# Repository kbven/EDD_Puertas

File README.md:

# Disseny de les portes

> **Autors:** Brandon Ventura, Pablo Peñalba.

> **Grup Mati**                             

--------

## Objectivo

Diseño de una una PCB para controlar las puertas.

## Especificaciones

* Mecanismo de motor para el alza cristales con un final de carrera.

* Implementación de mecanismo de seguridad anti-atrapamiento para la ventana con sensor de corriente.

* Sistema con motor por apertura y cierre de la puerta.

* Incluir un módulo de lectura RFID para apertura sin llave.
  
  ## Diagrama de Bloques

  ## Components

| Descripción               | Referencia          | Package   | Datasheet                                                                                                                                                                                                                                                                                                                                                                                                                                                                                  | Proveedor                                                                                                                                                                                                                                                                                                                                                                                                             | Precio/unidad | Cantidad |
|:-------------------------:|:-------------------:|:---------:|:------------------------------------------------------------------------------------------------------------------------------------------------------------------------------------------------------------------------------------------------------------------------------------------------------------------------------------------------------------------------------------------------------------------------------------------------------------------------------------------:|:---------------------------------------------------------------------------------------------------------------------------------------------------------------------------------------------------------------------------------------------------------------------------------------------------------------------------------------------------------------------------------------------------------------------:| ------------- | -------- |
| Microcontrolador          | PIC18F2580T-I/SO    | SOIC-28   | [datasheet](https://ww1.microchip.com/downloads/aemDocuments/documents/OTH/ProductDocuments/DataSheets/39637d.pdf)                                                                                                                                                                                                                                                                                                                                                                         | [DigiKey](https://www.digikey.es/es/products/detail/microchip-technology/PIC18F2580T-I-SO/739329?srsltid=AfmBOoqZu9kT-_KowIBzaAf4-_O7MsvTYlt4aUQzBQ2lc-jL20NezCRt)                                                                                                                                                                                                                                                    | 7,290 €       | 1        |
| Regulador de tensión-5V   | LM1117DT-5.0        | TO-252-3  | [datasheet](https://www.ti.com/lit/ds/symlink/lm1117.pdf?ts=1745298180828&ref_url=https%253A%252F%252Fwww.ti.com%252Fproduct%252FLM1117%253Futm_source%253Dgoogle%2526utm_medium%253Dcpc%2526utm_campaign%253Dapp-lp-null-44700045336317554_prodfolderdynamic-cpc-pf-google-eu_en_int%2526utm_content%253Dprodfolddynamic%2526ds_k%253DDYNAMIC+SEARCH+ADS%2526DCM%253Dyes%2526gclsrc%253Daw.ds%2526gad_source%253D1%2526gclid%253DEAIaIQobChMIy7u8je7qjAMVEbKDBx1GBzKxEAAYASAAEgJJMfD_BwE) | [Mouser](https://www.mouser.in/ProductDetail/Texas-Instruments/LM1117DT-5.0-NOPB?qs=X1J7HmVL2ZGITaQRKQ6NVA%3D%3D)                                                                                                                                                                                                                                                                                                     | 1,610 €       | 1        |
| Regulador de tensión 3,3V | LT1121IST-3.3       | SOT-223-3 | [datasheet](https://www.analog.com/media/en/technical-documentation/data-sheets/1121fg.pdf)                                                                                                                                                                                                                                                                                                                                                                                                | [DigiKey](https://www.digikey.at/en/products/detail/analog-devices-inc/LT1121IST-3-3-TRPBF/959066)                                                                                                                                                                                                                                                                                                                    | 8,190 €       | 1        |
| Cristal 8 MHz             | AA-8.000MALV-T      | SMD       | [datasheet](https://www.mouser.es/datasheet/2/417/aa_automotive-14929.pdf)                                                                                                                                                                                                                                                                                                                                                                                                                 | [Mouser](https://www.mouser.es/ProductDetail/TXC-Corporation/AA-8.000MALV-T?qs=02P6ycQEDWEs8mIQTVoxpQ%3D%3D)                                                                                                                                                                                                                                                                                                          | 0,779 €       | 1        |
| Pulsadores                | 3-1437565-0         | SMD       | [datasheet](https://www.mouser.es/datasheet/2/418/7/ENG_CD_2_1437565_7_V-2027970.pdf)                                                                                                                                                                                                                                                                                                                                                                                                      | [Mouser](https://www.mouser.es/ProductDetail/TE-Connectivity-PB/3-1437565-0?qs=%2FwXgF%2FfIho%2FDAgSy8ONeew%3D%3D)                                                                                                                                                                                                                                                                                                    | 0,266 €       | 5        |
| Transceiver               | MAX3051ESA+         | SOIC-8    | [datasheet](https://www.mouser.es/datasheet/2/609/MAX3051-3469944.pdf)                                                                                                                                                                                                                                                                                                                                                                                                                     | [Mouser](https://www.mouser.es/ProductDetail/Analog-Devices-Maxim-Integrated/MAX3051ESA+?qs=CDqwynd4ZNpXRaQ90S7BzQ%3D%3D)                                                                                                                                                                                                                                                                                             | 3,820 €       | 1        |
| Módulo RFID               | DLP-RFID2           | THT       | [datasheet](https://www.mouser.es/datasheet/2/117/dlp-rfid2-ds-v114-1374531.pdf)                                                                                                                                                                                                                                                                                                                                                                                                           | [Mouser](https://www.mouser.es/ProductDetail/DLP-Design/DLP-RFID2?qs=7edrXduW%2FNsZxdz8dNHO%2BQ%3D%3D)                                                                                                                                                                                                                                                                                                                | 36,050 €      | 1        |
| Conector coaxial          | Conector coaxial RS | THT       | [datasheet](https://docs.rs-online.com/062e/A700000007510792.pdf)                                                                                                                                                                                                                                                                                                                                                                                                                          | [RS](https://es.rs-online.com/web/p/conectores-coaxiales/5464049)                                                                                                                                                                                                                                                                                                                                                     | 9,630 €       | 1        |
| Sensor de Corriente       | IR2175STRPBF        | SOIC-8    | [datasheet](https://www.mouser.es/datasheet/2/196/Infineon_IR2175_S__DataSheet_v01_00_EN-3362704.pdf)                                                                                                                                                                                                                                                                                                                                                                                      | [Mouser](https://www.mouser.es/ProductDetail/Infineon-Technologies/IR2175STRPBF?qs=2r01AXMCG3Mz96toc2YS0Q%3D%3D)                                                                                                                                                                                                                                                                                                      | 3,080 €       | 1        |
| Relé de potencia          | G6E                 | THT       | [datasheet](https://docs.rs-online.com/8949/A700000008621017.pdf)                                                                                                                                                                                                                                                                                                                                                                                                                          | [RS](https://es.rs-online.com/web/p/reles-de-potencia/0376593)                                                                                                                                                                                                                                                                                                                                                        | 6,180 €       | 4        |
| Conector DB9              | 2311765-2           | THT       | [datasheet](https://www.mouser.es/datasheet/2/418/7/ENG_CD_2311765_D-2072969.pdf)                                                                                                                                                                                                                                                                                                                                                                                                          | [Mouser](https://www.mouser.es/ProductDetail/TE-Connectivity/2311765-2?qs=rrS6PyfT74frdzrH7SJRfg%3D%3D&mgh=1&vip=1&utm_id=19103542967&gad_source=1&gclid=CjwKCAjw26KxBhBDEiwAu6KXt0r6XHcXVAKDy0fb1AQDEcRaa8CqE_BUjWUK4OHCnLL84KZ4c8u68xoCDQcQAvD_BwE)                                                                                                                                                                 | 2,760 €       | 2        |
| MOSFET P-Channel          | AO3401A             | SOT-23-3  | [datasheet](https://www.aosmd.com/sites/default/files/res/datasheets/AO3401A.pdf)                                                                                                                                                                                                                                                                                                                                                                                                          | [Digikey](https://www.digikey.es/es/products/detail/alpha-omega-semiconductor-inc/AO3401A/1855773)                                                                                                                                                                                                                                                                                                                    | 0,420 €       | 4        |
| Led verde                 | LTST-C150KGKT       | 1206      | [datasheet](https://www.mouser.es/datasheet/2/239/LTST_C150KGKT-1143771.pdf)                                                                                                                                                                                                                                                                                                                                                                                                               | [Mouser](https://www.mouser.es/ProductDetail/LITEON/LTST-C150KGKT?qs=G7lFeYdtIHB%2FzaFKBwEyXw%3D%3D)                                                                                                                                                                                                                                                                                                                  | 0,171 €       | 1        |
| Pin Header 1x3            | 61300311121         | THT       | [datasheet](https://www.we-online.com/components/products/datasheet/61300311121.pdf)                                                                                                                                                                                                                                                                                                                                                                                                       | [DigiKey](https://www.digikey.es/es/products/detail/w%C3%BCrth-elektronik/61300311121/4846825?utm_adgroup=&utm_source=google&utm_medium=cpc&utm_campaign=PMax_Supplier_W%C3%BCrth%20Elektronik&utm_term=&utm_content=&utm_id=go_cmp-20673490314_adg-_ad-__dev-c_ext-_prd-4846825_sig-CjwKCAjw26KxBhBDEiwAu6KXt-nrzPnR6AizAc4OFYg5FhEvs2IVS_BrHZ7kmUmR4I-WiUOawUIyVxoCUwUQAvD_BwE&gad_source=1)                        | 0,110 €       | 1        |
| Pin Header 1x5            | 61300511121         | THT       | [datasheet](https://www.we-online.com/components/products/datasheet/61300511121.pdf)                                                                                                                                                                                                                                                                                                                                                                                                       | [DigiKey](https://www.digikey.es/es/products/detail/w-rth-elektronik/61300511121/4846831?gclsrc=aw.ds&&utm_adgroup=&utm_source=google&utm_medium=cpc&utm_campaign=PMax_Supplier_W%C3%BCrth%20Elektronik&utm_term=&utm_content=&utm_id=go_cmp-20673490314_adg-_ad-__dev-c_ext-_prd-4846831_sig-Cj0KCQjw_JzABhC2ARIsAPe3ynqs6H_uQKrXoszVjdwNbumXRq61QB8zz5D_9xSB8SHJlS3C75W4jUcaAgxDEALw_wcB&gad_source=1&gclsrc=aw.ds) | 0,220 €       | 3        |
| Connector screw 1x2       | 1729128             | ---       | [datasheet](https://www.phoenixcontact.com/en-us/products/printed-circuit-board-terminal-mkdsn-15-2-508-1729128?type=pdf)                                                                                                                                                                                                                                                                                                                                                                  | [Mouser](https://www.mouser.es/ProductDetail/Phoenix-Contact/1729128?qs=GFUSqQMLmmnCBVBY3dts9w%3D%3D&mgh=1&vip=1&utm_id=19103542967&gad_source=1)                                                                                                                                                                                                                                                                     | 1,020 €       | 3        |
| Connector screw 1x3       | 1751251             | ---       | [datasheet](https://www.phoenixcontact.com/en-us/products/printed-circuit-board-terminal-mkds-1-3-35-1751251?type=pdf)                                                                                                                                                                                                                                                                                                                                                                     | [Mouser](https://www.mouser.es/ProductDetail/Phoenix-Contact/1751251?qs=wdlOgCqRo4w4Go2awGHrzA%3D%3D&mgh=1&vip=1&utm_id=19103542967&utm_source=google&utm_medium=cpc&utm_marketing_tactic=emeacorp&gad_source=1&gclid=CjwKCAjwn6LABhBSEiwAsNJrjgZZoCVfRYw56vXbadD5RguB0HYuv-8IHCZePBymYZpktI2TEDrjRBoCaIAQAvD_BwE)                                                                                                    | 1,680 €       | 2        |
| Resistencias 10K          | RK73G2BTTD1002F     | 1206      | [datasheet](https://www.koaspeer.com/pdfs/RK73G.pdf)                                                                                                                                                                                                                                                                                                                                                                                                                                       | [Mouser](https://www.mouser.es/ProductDetail/KOA-Speer/RK73G2BTTD1002F?qs=sGAEpiMZZMtlubZbdhIBIDot9%252BiNsVp%2FQ8bvR3gz9R8%3D)                                                                                                                                                                                                                                                                                       | 0,241 €       | 15       |
| Resistencia 60            | RP73PF1J60R4BTDF    | 0603      | [datasheet](https://www.mouser.es/datasheet/2/418/10/ENG_DS_1773272_M1-1588495.pdf)                                                                                                                                                                                                                                                                                                                                                                                                        | [Mouser](https://www.mouser.es/ProductDetail/TE-Connectivity-Holsworthy/RP73PF1J60R4BTDF?qs=gt1LBUVyoHkLKYO0jJjvhA%3D%3D)                                                                                                                                                                                                                                                                                             | 0,456 €       | 1        |
| Resistencia 1K            | RNCA0603BTE1K00     | 0603      | [datasheet](https://www.mouser.es/datasheet/2/385/SEI_RNCA-3473065.pdf)                                                                                                                                                                                                                                                                                                                                                                                                                    | [Mouser](https://www.mouser.es/ProductDetail/SEI-Stackpole/RNCA0603BTE1K00?qs=i8QVZAFTkqR0RAUMHohaTQ%3D%3D)                                                                                                                                                                                                                                                                                                           | 0,228 €       | 1        |
| Resistencia shunt         | WSHM2818R1000FEA    | SMD       | [datasheet](https://www.vishay.com/docs/30188/wshm2818.pdf)                                                                                                                                                                                                                                                                                                                                                                                                                                | [Mouser](https://www.mouser.es/ProductDetail/Vishay-Dale/WSHM2818R1000FEA?qs=sGAEpiMZZMtlleCFQhR%2FzR2tSEfVSrFZ5FX0iCqyh4mr%252BZVUTZXBeA%3D%3D)                                                                                                                                                                                                                                                                      | 1,370 €       | 1        |
| 10u                       | ECA-1CHG101I        | THT       | [datasheet](https://industrial.panasonic.com/cdbs/www-data/pdf/RDF0000/ABA0000C1218.pdf)                                                                                                                                                                                                                                                                                                                                                                                                   | [Mouser](https://www.mouser.es/ProductDetail/Panasonic/ECA-1CM100I?qs=fcM5arftASvKR70PPIzFqA%3D%3D)                                                                                                                                                                                                                                                                                                                   | 0,152 €       | 3        |
| 1u                        | C0805C105K4RACAUTO  | 0805      | [datasheet](https://www.mouser.es/datasheet/2/447/KEM_C1023_X7R_AUTO_SMD-3316698.pdf)                                                                                                                                                                                                                                                                                                                                                                                                      | [Mouser](https://www.mouser.es/ProductDetail/KEMET/C0805C105K4RACAUTO?qs=OHu5RF0w3QprP0D5VzlqaQ%3D%3D)                                                                                                                                                                                                                                                                                                                | 0,152 €       | 1        |
| 100n                      | C1206C104K4RACTU    | 1206      | [datasheet](https://www.mouser.es/datasheet/2/447/KEM_C1002_X7R_SMD-3316098.pdf)                                                                                                                                                                                                                                                                                                                                                                                                           | [Mouser](https://www.mouser.es/ProductDetail/KEMET/C1206C104K4RACTU?qs=NAOyRStS94fKvqJx0gg6JQ%3D%3D)                                                                                                                                                                                                                                                                                                                  | 0,095 €       | 7        |
| 21p                       | 0504N220J500P       | 0504      | [datasheet](https://www.knowlescapacitors.com/getattachment/ddd08fe0-16c1-4f86-944e-edc3fc04fb57/X7R.aspx)                                                                                                                                                                                                                                                                                                                                                                                 | [DigiKey](https://www.digikey.es/es/products/detail/knowles-novacap/0504N220J500P/21849946?s=N4IgjCBcpgbFoDGUBmBDANgZwKYBoQB7KAbRAGYBOAJjAHYQBdAgBwBcoQBlNgJwEsAdgHMQAXwLUADABZKCEMkjps%2BIqRDVqAAhYAxJqw6QQAVUH82AeRQBZHGiwBXXjnETNGxGhZpElwl5tLABbABMmMSA)                                                                                                                                                          | 0,620 €       | 2        |
| D6,D7,D8,D9               | SR1202 A0G          | THT       | [datasheet](https://services.taiwansemi.com/storage/resources/datasheet/SR1202%20SERIES_G2105.pdf)                                                                                                                                                                                                                                                                                                                                                                                         | [Mouser](https://www.mouser.es/ProductDetail/Taiwan-Semiconductor/SR1202-A0G?qs=mAH9sUMRCtsYw%2FEG19A30A%3D%3D)                                                                                                                                                                                                                                                                                                       | 0,384 €       | 4        |
| D4,D5                     | SBR12A45SD1-T       | THT       | [datasheet](https://www.diodes.com/assets/Datasheets/SBR12A45SD1.pdf)                                                                                                                                                                                                                                                                                                                                                                                                                      | [Mouser](https://www.mouser.es/ProductDetail/Diodes-Incorporated/SBR12A45SD1-T?qs=oUsD4qhOtFxVeI%252BTfVYIRA%3D%3D)                                                                                                                                                                                                                                                                                                   | 0,485 €       | 2        |
| D2                        | SR1203H             | THT       | [datasheet](https://services.taiwansemi.com/storage/resources/datasheet/SR1202%20SERIES_G2105.pdf)                                                                                                                                                                                                                                                                                                                                                                                         | [Mouser](https://www.mouser.es/ProductDetail/Taiwan-Semiconductor/SR1203H?qs=sGAEpiMZZMvplms98TlKY%2FeyDi3uMxFUBy2aTn9D5Xra285XE8SMsA%3D%3D)                                                                                                                                                                                                                                                                          | 0,384 €       | 1        |
| D3                        | SBR10U45SD1-T       | THT       | [datasheet](https://www.diodes.com/assets/Datasheets/SBR10U45SD1.pdf)                                                                                                                                                                                                                                                                                                                                                                                                                      | [Mouser](https://www.mouser.es/ProductDetail/Diodes-Incorporated/SBR10U45SD1-T?qs=oUsD4qhOtFyWKufSWj8qkg%3D%3D)                                                                                                                                                                                                                                                                                                       | 0,912 €       | 1        |

##Motores y final de carrera

| Descripción      | Referencia                      | Datasheet                                                         | Proveedor                                                                     | Cantidad |
|:----------------:|:-------------------------------:|:-----------------------------------------------------------------:|:-----------------------------------------------------------------------------:| -------- |
| Motor Lineal     | Actuador lineal 12VDC 800N 2,9A |                                                                   | [Transmotec](https://www.transmotec.es/product/dla-12-30-a-50-ip65/?vat=true) | 1        |
| Motor DC         | Motor DC RS PRO                 | [datasheet](https://docs.rs-online.com/6e47/A700000007082069.pdf) | [Rs](https://es.rs-online.com/web/p/motores-dc/3213186)                       | 1        |
| Final de carrera | Palanca de Rodillo RS PRO       | [datasheet](https://docs.rs-online.com/2b32/A700000008919438.pdf) | [Rs](https://es.rs-online.com/web/p/interruptores-final-de-carrera/9026871)   | 2        |

## Historial de cambios

| Data       | Autor               | Branch | Descripción                                                                             |
| ---------- | ------------------- | ------ | --------------------------------------------------------------------------------------- |
| 26/03/2025 | B.Ventura           | Main   | Readme y Esquemático                                                                    |
| 26/03/2025 | B.Ventura           | Main   | Diagrama de Bloques                                                                     |
| 28/03/2025 | B.Ventura           | Main   | Terminales y Diodos                                                                     |
| 28/03/2025 | P.Peñalba           | Main   | Etiquetas,Botonera y Buck converter                                                     |
| 01/04/2025 | B.Ventura           | Main   | Corrección del esquema, terminal screw terminals y layout v1                            |
| 09/04/2025 | B.Ventura           | Main   | cambio de posición pines, cambio de terminales final de carrera y corrección error grid |
| 09/04/2025 | B.Ventura/P.Peñalba | Main   | layout versión 2, reglas de diseño JLCPCB                                               |
| 12/04/2025 | B.Ventura/P.Peñalba | Main   | Corrección de las pistas layout y planos                                                |
| 21/04/2025 | B.Ventura           | Main   | Presupuesto                                                                             |

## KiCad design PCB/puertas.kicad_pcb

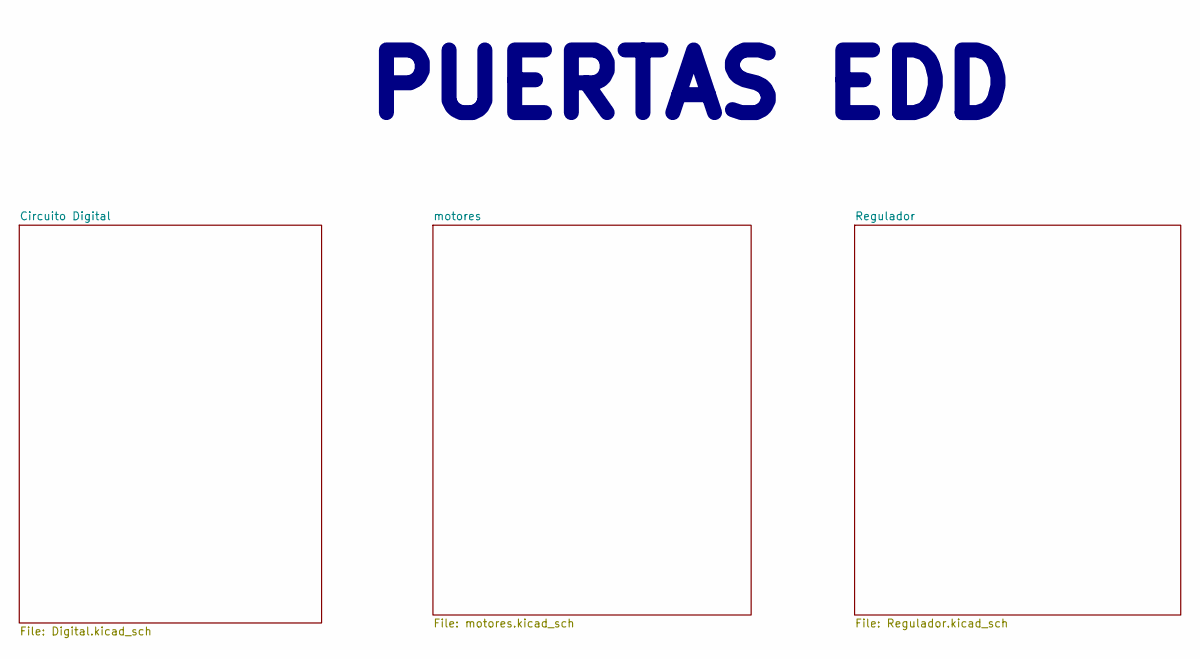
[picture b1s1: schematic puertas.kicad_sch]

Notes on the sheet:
PUERTAS EDD

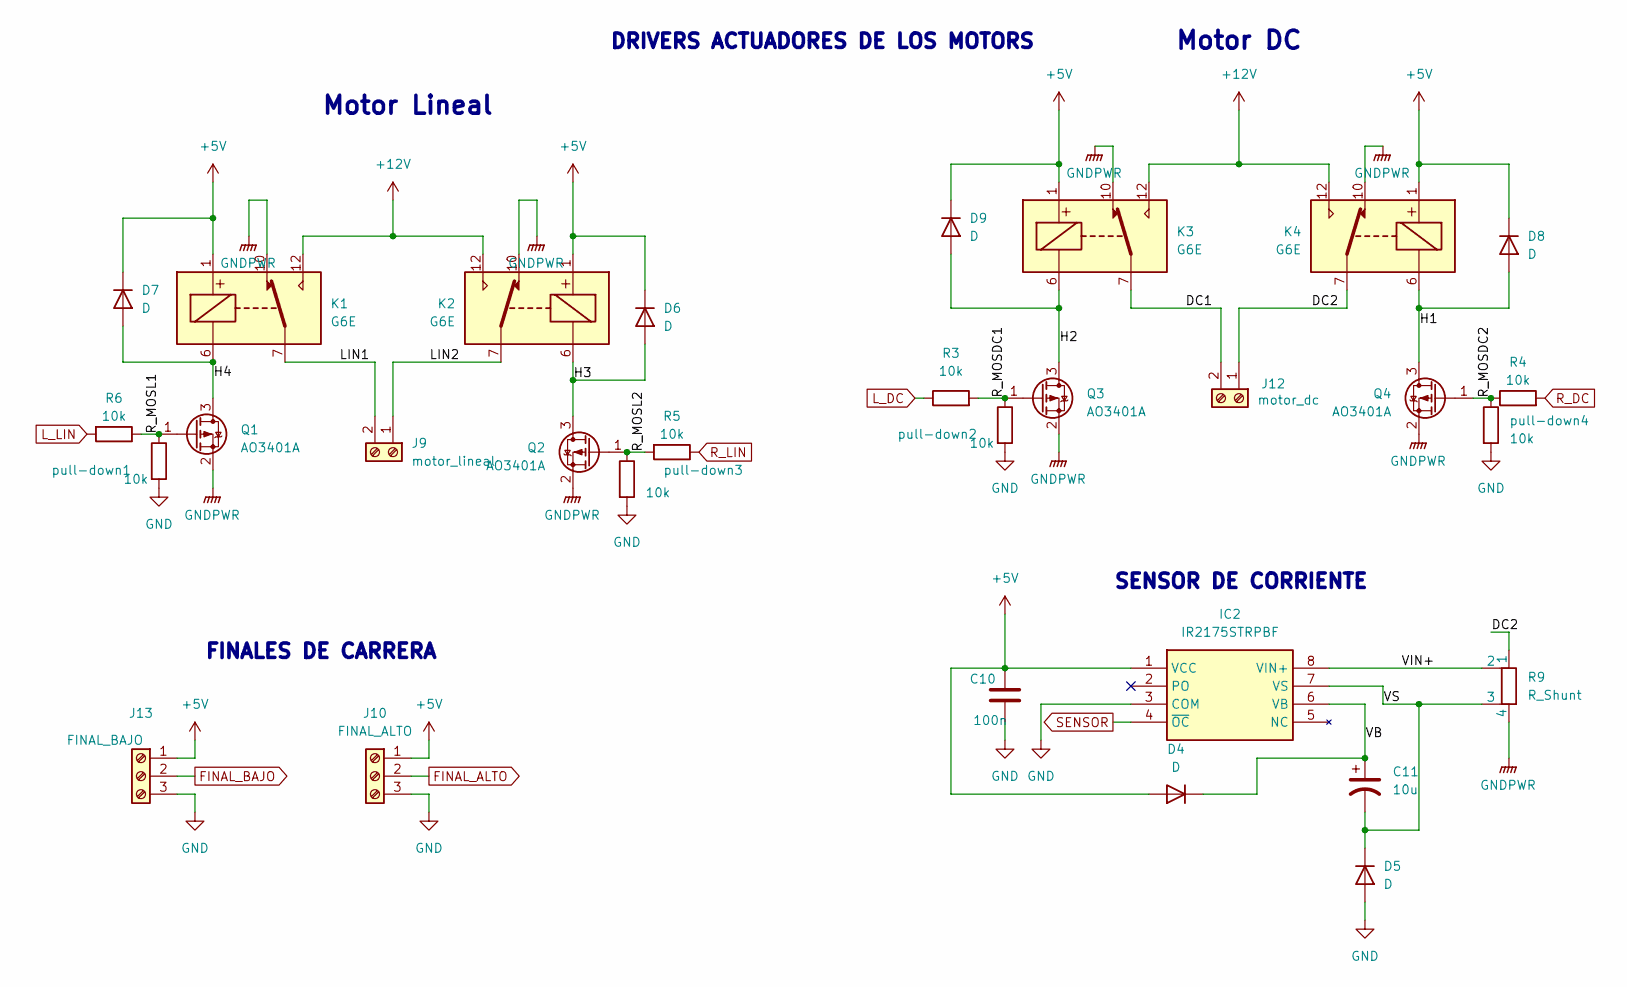
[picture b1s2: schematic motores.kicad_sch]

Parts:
C10: 100n; C_1206_3216Metric
C11: 10u; CP_Radial_D6.3mm_P2.50mm
D4, D5, D6, D7, D8, D9: D; D_DO-201AD_P12.70mm_Horizontal
IC2: IR2175STRPBF; SOIC127P600X175-8N; Mouser Part Number 942-IR2175STRPBF
J9: motor_lineal; TerminalBlock_Phoenix_MKDS-3-2-5.08_1x02_P5.08mm_Horizontal
J10: FINAL_ALTO; TerminalBlock_Phoenix_MKDS-3-3-5.08_1x03_P5.08mm_Horizontal
J12: motor_dc; TerminalBlock_Phoenix_MKDS-3-2-5.08_1x02_P5.08mm_Horizontal
J13: FINAL_BAJO; TerminalBlock_Phoenix_MKDS-3-3-5.08_1x03_P5.08mm_Horizontal
K1, K2, K3, K4: G6E; Relay_SPDT_Omron_G6E
Q1, Q2, Q3, Q4: AO3401A; SOT-23
R3, R4, R5, R6: 10k; R_1206_3216Metric
R9: R_Shunt; R_Shunt_Ohmite_LVK25
pull-down1, pull-down2, pull-down3, pull-down4: 10k; C_1206_3216Metric

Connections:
+5V: C10.1, D4.2 (A), D6.1 (K), D7.1 (K), D8.1 (K), D9.1 (K), IC2.1 (VCC), J10.1, J13.1, K1.1, K2.1, K3.1, K4.1; also elsewhere on the board
+12V: K1.12, K2.12, K3.12, K4.12; also elsewhere on the board
/motores/DC1: J12.2, K3.7
/motores/DC2: J12.1, K4.7, R9.1
/motores/H1: D8.2 (A), K4.6, Q4.3 (D)
/motores/H2: D9.2 (A), K3.6, Q3.3 (D)
/motores/H3: D6.2 (A), K2.6, Q2.3 (D)
/motores/H4: D7.2 (A), K1.6, Q1.3 (D)
/motores/LIN1: J9.2, K1.7
/motores/LIN2: J9.1, K2.7
/motores/R_MOSDC1: Q3.1 (G), R3.2, pull-down2.1
/motores/R_MOSDC2: Q4.1 (G), R4.1, pull-down4.1
/motores/R_MOSL1: Q1.1 (G), R6.1, pull-down1.1
/motores/R_MOSL2: Q2.1 (G), R5.2, pull-down3.1
/motores/VB: C11.1, D4.1 (K), IC2.6 (VB)
/motores/VIN+: IC2.8 (VIN+), R9.2
/motores/VS: C11.2, D5.1 (K), IC2.7 (VS), R9.3
FINAL_ALTO: J10.2; also elsewhere on the board
FINAL_BAJO: J13.2; also elsewhere on the board
GND: C10.2, D5.2 (A), IC2.3 (COM), J10.3, J13.3, pull-down1.2, pull-down2.2, pull-down3.2, pull-down4.2; also elsewhere on the board
GNDPWR: K1.10, K2.10, K3.10, K4.10, Q1.2 (S), Q2.2 (S), Q3.2 (S), Q4.2 (S), R9.4; also elsewhere on the board
L_DC: R3.1; also elsewhere on the board
L_LIN: R6.2; also elsewhere on the board
R_DC: R4.2; also elsewhere on the board
R_LIN: R5.1; also elsewhere on the board
SENSOR: IC2.4 (~OC); also elsewhere on the board

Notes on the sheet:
FINALES DE CARRERA
Motor DC
Motor Lineal
DRIVERS ACTUADORES DE LOS MOTORS
SENSOR DE CORRIENTE

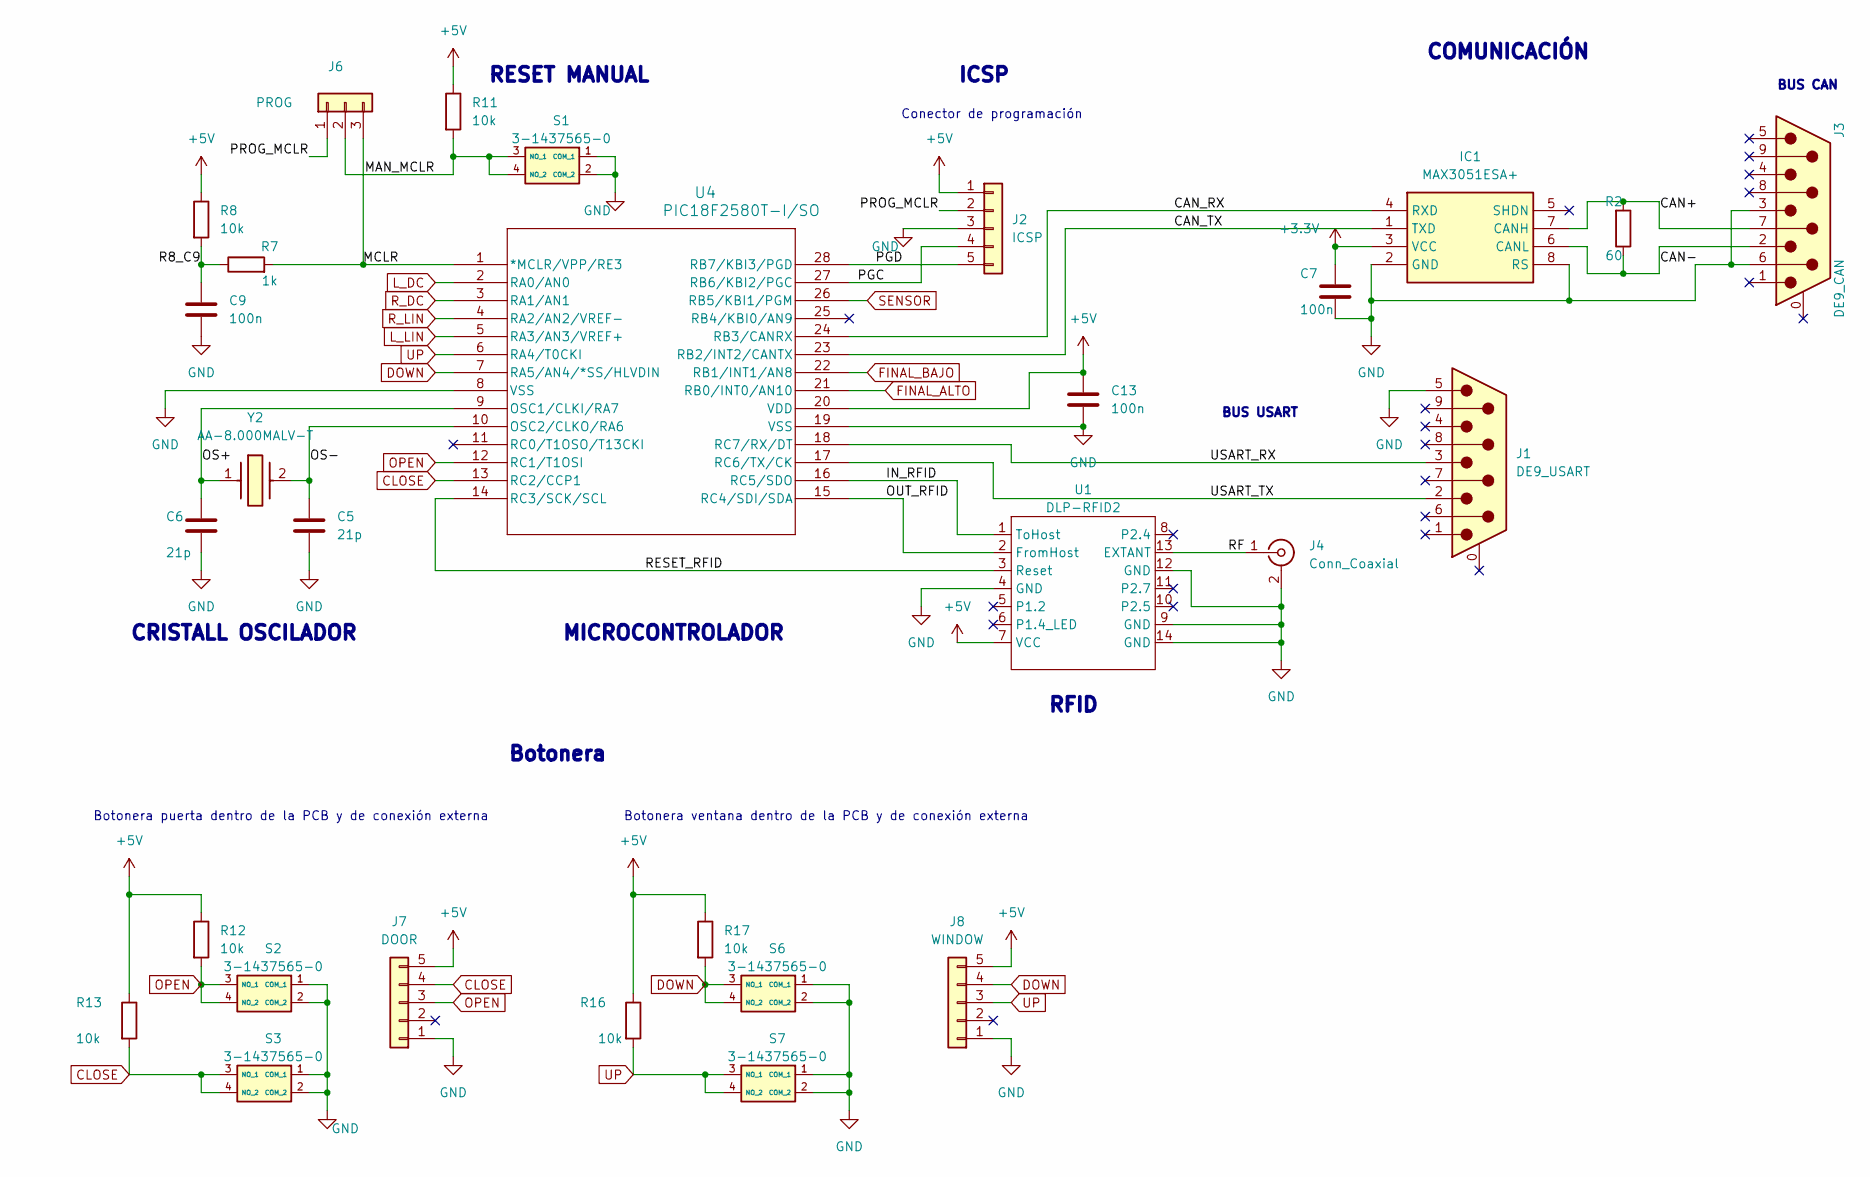
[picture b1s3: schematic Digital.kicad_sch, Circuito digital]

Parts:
C5, C6: 21p; C_0504_1310Metric
C7, C9, C13: 100n; C_1206_3216Metric
IC1: MAX3051ESA+; SOIC127P600X175-8N; Mouser Part Number 700-MAX3051ESA
J1: DE9_USART; DSUB-9_Pins_Horizontal_P2.77x2.84mm_EdgePinOffset4.94mm_Hou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
J2: ICSP; PinHeader_1x05_P2.54mm_Vertical
J3: DE9_CAN; DSUB-9_Pins_Horizontal_P2.77x2.84mm_EdgePinOffset4.94mm_Hou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; LCSC C575183
J4: Conn_Coaxial; BNC_TEConnectivity_1478035_Horizontal
J6: PROG; PinHeader_1x03_P2.54mm_Vertical
J7: DOOR; PinHeader_1x05_P2.54mm_Vertical
J8: WINDOW; PinHeader_1x05_P2.54mm_Vertical
R2: 60; R_0603_1608Metric; LCSC C22787
R7: 1k; R_0603_1608Metric
R8: 10k; R_1206_3216Metric
R11, R12, R13, R16, R17: 10k; C_1206_3216Metric
S1, S2, S3, S6, S7: 3-1437565-0; 314375650; Mouser Part Number 506-3-1437565-0
U1: DLP-RFID2
U4: PIC18F2580T-I/SO; SOIC28-W_MC_MCH
Y2: AA-8.000MALV-T; AA8000MALVT; Mouser Part Number 717-AA-8.000MALV-T

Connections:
+3.3V: C7.1, IC1.3 (VCC); also elsewhere on the board
+5V: C13.1, J2.1, J7.5, J8.5, R8.1, R11.1, R12.1, R13.1, R16.1, R17.1, U1.7 (VCC), U4.20 (VDD); also elsewhere on the board
/Circuito Digital/CAN+: IC1.7 (CANH), J3.7, R2.2
/Circuito Digital/CAN-: IC1.6 (CANL), J3.2, R2.1
/Circuito Digital/CAN_RX: IC1.4 (RXD), U4.24 (RB3/CANRX)
/Circuito Digital/CAN_TX: IC1.1 (TXD), U4.23 (RB2/INT2/CANTX)
/Circuito Digital/IN_RFID: U1.1 (ToHost), U4.16 (RC5/SDO)
/Circuito Digital/MAN_MCLR: J6.2, R11.2, S1.3 (NO_1), S1.4 (NO_2)
/Circuito Digital/MCLR: J6.3, R7.2, U4.1 (*MCLR/VPP/RE3)
/Circuito Digital/OS+: C6.1, U4.9 (OSC1/CLKI/RA7), Y2.1
/Circuito Digital/OS-: C5.1, U4.10 (OSC2/CLKO/RA6), Y2.2
/Circuito Digital/OUT_RFID: U1.2 (FromHost), U4.15 (RC4/SDI/SDA)
/Circuito Digital/PGC: J2.4, U4.27 (RB6/KBI2/PGC)
/Circuito Digital/PGD: J2.5, U4.28 (RB7/KBI3/PGD)
/Circuito Digital/PROG_MCLR: J2.2, J6.1
/Circuito Digital/R8_C9: C9.1, R7.1, R8.2
/Circuito Digital/RESET_RFID: U1.3 (Reset), U4.14 (RC3/SCK/SCL)
/Circuito Digital/RF: J4.1 (In), U1.13 (EXTANT)
/Circuito Digital/USART_RX: J1.3, U4.18 (RC7/RX/DT)
/Circuito Digital/USART_TX: J1.2, U4.17 (RC6/TX/CK)
CLOSE: J7.4, R13.2, S3.3 (NO_1), S3.4 (NO_2), U4.13 (RC2/CCP1)
DOWN: J8.4, R17.2, S6.3 (NO_1), S6.4 (NO_2), U4.7 (RA5/AN4/*SS/HLVDIN)
FINAL_ALTO: U4.21 (RB0/INT0/AN10); also elsewhere on the board
FINAL_BAJO: U4.22 (RB1/INT1/AN8); also elsewhere on the board
GND: C5.2, C6.2, C7.2, C9.2, C13.2, IC1.2 (GND), IC1.8 (RS), J1.5, J2.3, J3.3, J3.6, J4.2 (Ext), J7.1, J8.1, S1.1 (COM_1), S1.2 (COM_2), S2.1 (COM_1), S2.2 (COM_2), S3.1 (COM_1), S3.2 (COM_2), S6.1 (COM_1), S6.2 (COM_2), S7.1 (COM_1), S7.2 (COM_2), U1.4 (GND), U1.9 (GND), U1.12 (GND), U1.14 (GND), U4.8 (VSS), U4.19 (VSS); also elsewhere on the board
L_DC: U4.2 (RA0/AN0); also elsewhere on the board
L_LIN: U4.5 (RA3/AN3/VREF+); also elsewhere on the board
OPEN: J7.3, R12.2, S2.3 (NO_1), S2.4 (NO_2), U4.12 (RC1/T1OSI)
R_DC: U4.3 (RA1/AN1); also elsewhere on the board
R_LIN: U4.4 (RA2/AN2/VREF-); also elsewhere on the board
SENSOR: U4.26 (RB5/KBI1/PGM); also elsewhere on the board
UP: J8.3, R16.2, S7.3 (NO_1), S7.4 (NO_2), U4.6 (RA4/T0CKI)

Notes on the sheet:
CRISTALL OSCILADOR
BUS USART
RESET MANUAL
Botonera
RFID
COMUNICACIÓN
MICROCONTROLADOR
Botonera puerta dentro de la PCB y de conexión externa
ICSP
Conector de programación
BUS CAN
Botonera ventana dentro de la PCB y de conexión externa

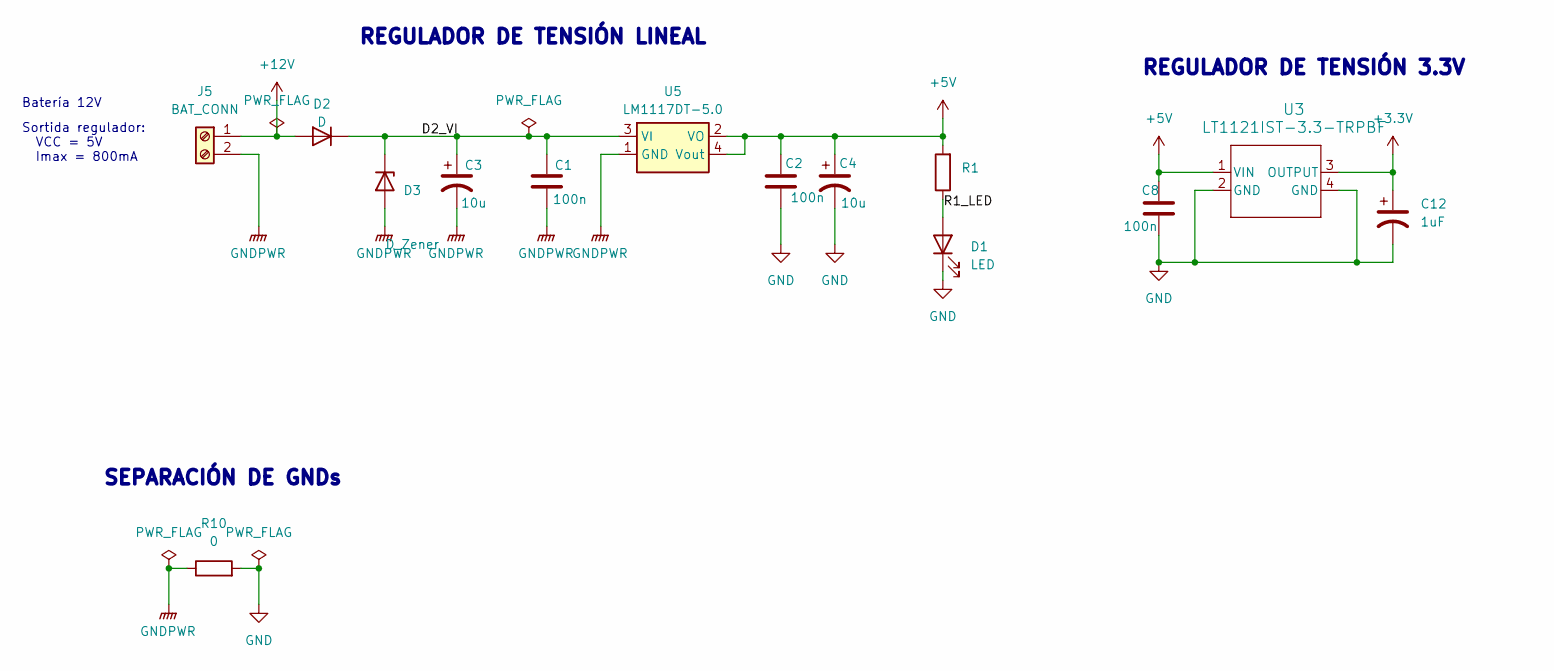
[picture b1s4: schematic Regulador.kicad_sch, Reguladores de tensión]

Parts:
C1, C2, C8: 100n; C_1206_3216Metric
C3, C4: 10u; CP_Radial_D5.0mm_P2.50mm
C12: 1uF; C_0805_2012Metric
D1: LED; LED_1206_3216Metric
D2: D; D_DO-201AD_P12.70mm_Horizontal
D3: D_Zener; D_DO-15_P12.70mm_Horizontal
J5: BAT_CONN; TerminalBlock_Phoenix_MKDS-3-2-5.08_1x02_P5.08mm_Horizontal
R1: 10K; R_1206_3216Metric_Pad1.30x1.75mm_HandSolder
R10: 0; C_1206_3216Metric
U3: LT1121IST-3.3-TRPBF; SOT-223_ST_LIT
U5: LM1117DT-5.0; TO-252-3_TabPin2

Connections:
+3.3V: C12.1, U3.3 (OUTPUT); also elsewhere on the board
+5V: C2.1, C4.1, C8.1, R1.2, U3.1 (VIN), U5.2 (VO), U5.4 (Vout); also elsewhere on the board
+12V: D2.2 (A), J5.1; also elsewhere on the board
/Regulador/D2_VI: C1.1, C3.1, D2.1 (K), D3.1 (K), U5.3 (VI)
/Regulador/R1_LED: D1.2 (A), R1.1
GND: C2.2, C4.2, C8.2, C12.2, D1.1 (K), R10.2, U3.2 (GND), U3.4 (GND); also elsewhere on the board
GNDPWR: C1.2, C3.2, D3.2 (A), J5.2, R10.1, U5.1 (GND); also elsewhere on the board

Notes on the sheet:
SEPARACIÓN DE GNDs
Sortida regulador: VCC = 5V Imax = 800mA
REGULADOR DE TENSIÓN 3.3V
REGULADOR DE TENSIÓN LINEAL
Batería 12V

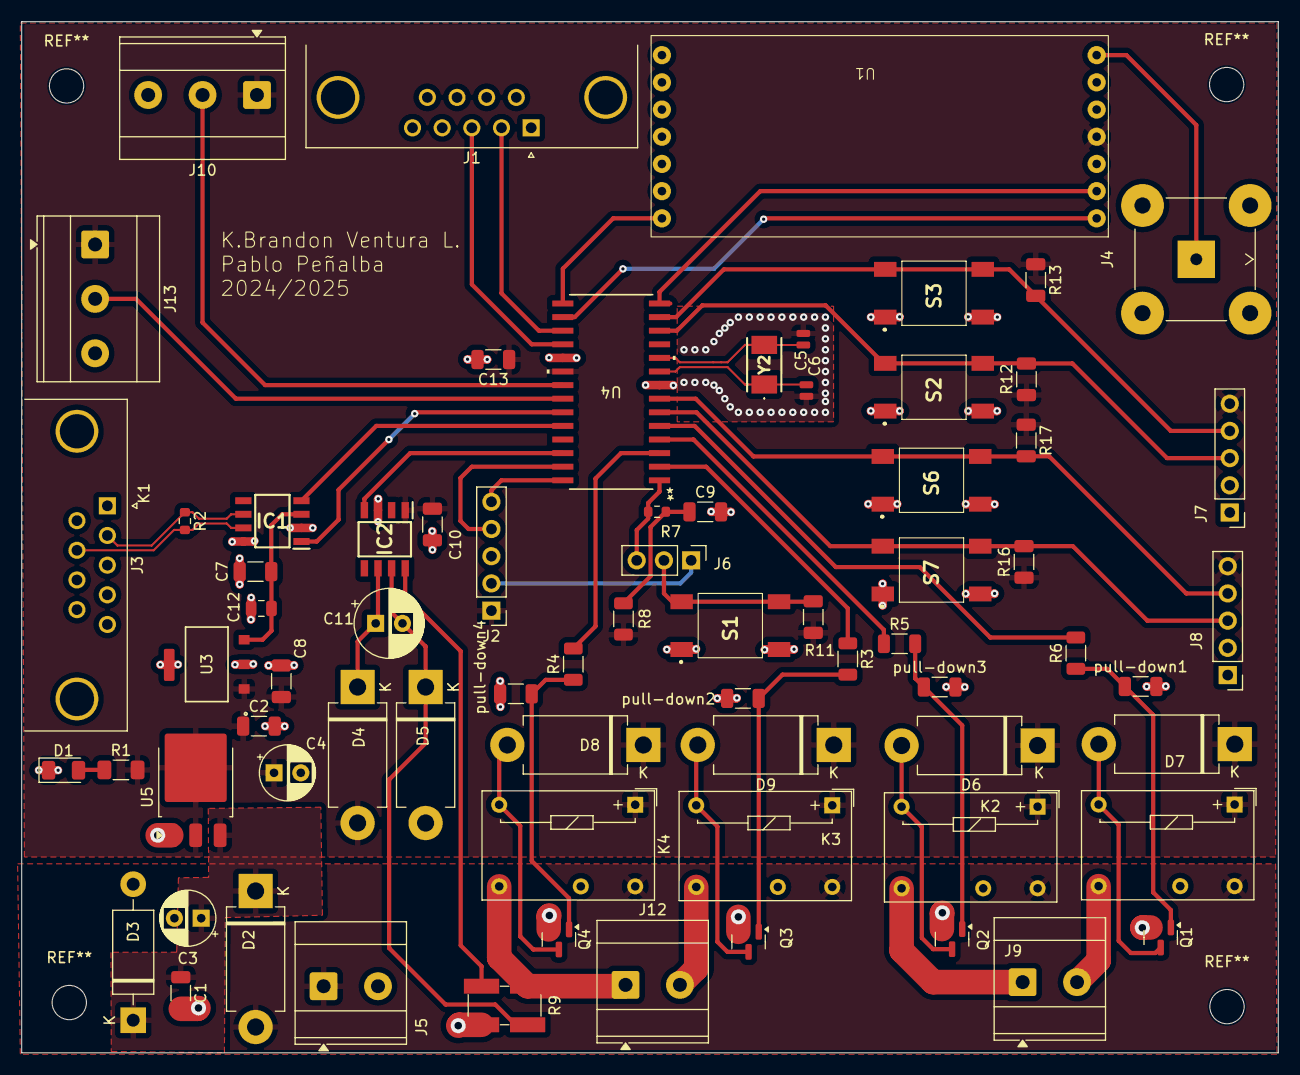
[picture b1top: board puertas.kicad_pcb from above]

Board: 2 copper layers, 117.3 x 96.3 mm, 73 parts (1 on the bottom side), 51 nets.

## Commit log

2025-03-21 Backlink to CADLAB.io has been added.
2025-03-26 Esquema
2025-03-26 Circuit failed cadlab corregido
2025-03-26 Error:Circuit_Circuit_failed_to_process
2025-03-26 diagrama bloques
2025-03-26 diagrama de bloques
2025-03-26 carpeta componentes
2025-03-28 Terminales y Diodos
    Terminales de motor tipo screw y diodos de relés
2025-03-28 Test commit
    valores de condensadores de cristal
2025-03-29 added datasheets for buck, ldo and button
2025-03-29 modificado el LM1117 a la versión TO-252 de 3 patas y salida no ajustable a 5V. Añadido el coil de salida 82683C para el BUCK a la librería
2025-03-29 conectados directamente los relés a los conectores
2025-03-29 anadido el shdn directo al PIC. Es un pin de alarma térmica del transceiver. El sensor de corriente está mal hay que darle una vuelta
2025-03-29 added datasheet
2025-03-30 Condesnadors buck converter
2025-04-01 Update README.md
    componentes i datasheet añadido
2025-04-02 layout
2025-04-02 layout pre
2025-04-02 directorio doc, presentación
2025-04-02 Nuevo Crystal
2025-04-02 esquemático v2
2025-04-05 Fixed motors
    mosfet shcematic fix
2025-04-05 Changed LM1117
2025-04-05 smaller d2
    0603
2025-04-05 smaller C3
2025-04-05 smaller diodes for rele
2025-04-05 changed relay
2025-04-09 Fixed labels and ERC errors
2025-04-09 ADDED footprint RFID lector
2025-04-09 cambio de posición de los pines
2025-04-09 cambio de terminales tipo screw, final de carrera
2025-04-09 corrección de error de grid
2025-04-09 corrección error grid
2025-04-09 corrección error grid
2025-04-09 layout v2, reglas jlcpcb
2025-04-09 added links for diodes to mouser.md
2025-04-09 ancho de pista de gnd, corrección de ruteado
    corrección de separación de plano de +5V, ancho de pista coincidente con gnd
2025-04-23 Componentes PCB
2025-04-24 Gerbers
2025-04-24 Update PCB
2025-04-24 Delete PCB/sym-lib-table
    no utilizado
2025-04-24 archivo BOM
2025-04-24 Coste de fabricación
2025-04-24 Presentacion
2025-04-24 Presupuesto
2025-04-24 Rename digrama_bloques.png to diagrama_bloques.png
2025-04-24 rename
